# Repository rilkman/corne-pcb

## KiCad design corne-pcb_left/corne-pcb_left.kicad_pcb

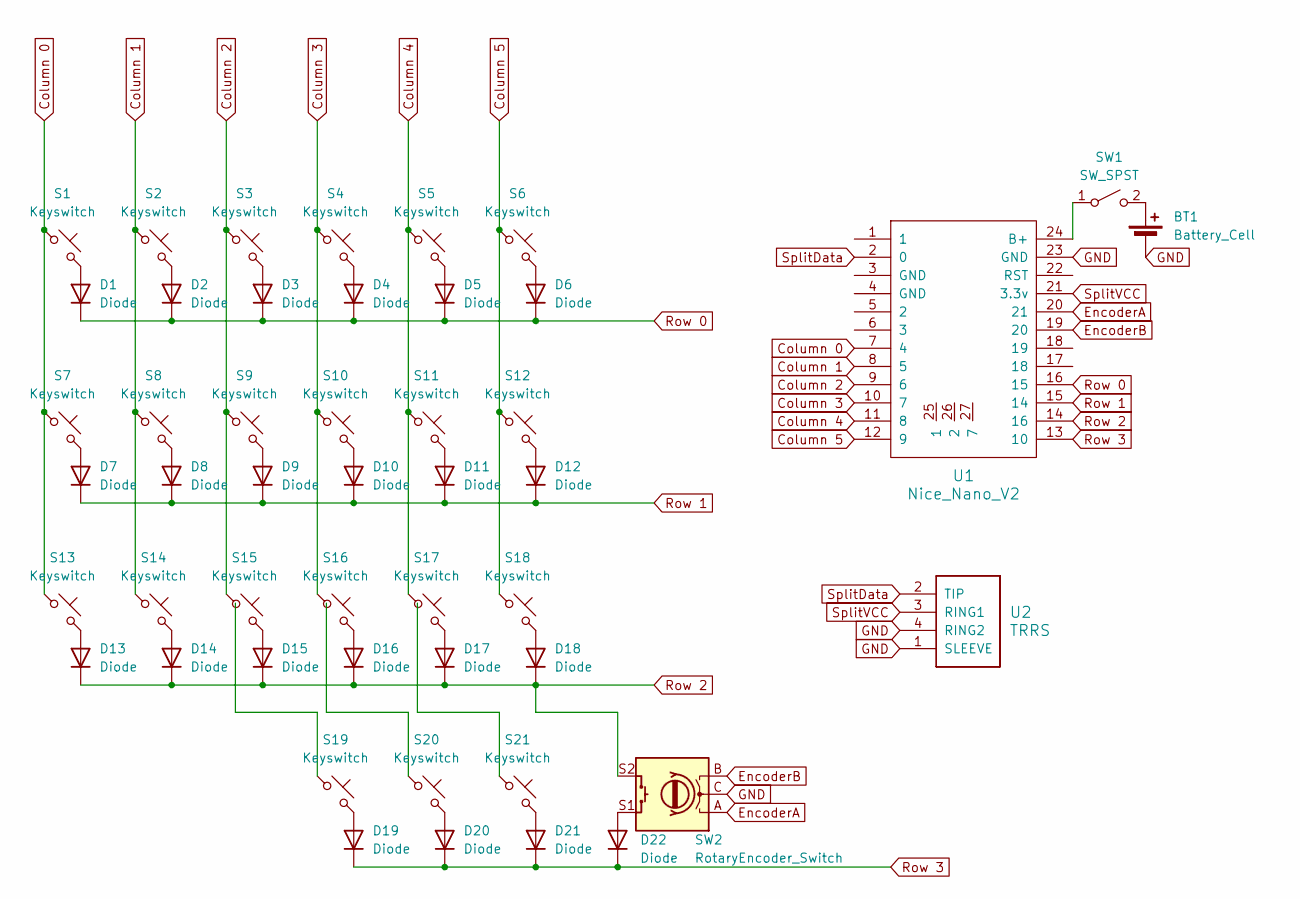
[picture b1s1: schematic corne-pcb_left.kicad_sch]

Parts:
BT1: Battery_Cell; JST_PH_S2B-PH-K_1x02_P2.00mm_Horizontal
D1, D2, D3, D4, D5, D6, D7, D8, D9, D10, D11, D12, D13, D14, D15, D16, D17, D18, D19, D20, D21, D22: Diode; Diode_SOD-123
S1, S2, S3, S4, S5, S6, S7, S8, S9, S10, S11, S12, S13, S14, S15, S16, S17, S18, S19, S20: Keyswitch; Hotswap_Choc_V1_1.00u
S21: Keyswitch; Hotswap_Choc_V1_1.50u_90deg
SW1: SW_SPST; SW_Slide_SPDT_Straight_CK_OS102011MS2Q
SW2: RotaryEncoder_Switch; Encoder_EC11_MX
U1: Nice_Nano_V2
U2: TRRS; TRRS_PJ-320A

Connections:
Column 0: S1.1, S7.1, S13.1, U1.7 (4)
Column 1: S2.1, S8.1, S14.1, U1.8 (5)
Column 2: S3.1, S9.1, S15.1, U1.9 (6)
Column 3: S4.1, S10.1, S16.1, U1.10 (7)
Column 4: S5.1, S11.1, S17.1, U1.11 (8)
Column 5: S6.1, S12.1, S18.1, U1.12 (9)
EncoderA: SW2.A, U1.20 (21)
EncoderB: SW2.B, U1.19 (20)
GND: BT1.2 (-), SW2.C, U1.23 (GND), U2.1 (SLEEVE), U2.4 (RING2)
unnamed: BT1.1 (+), SW1.2 (B)
unnamed: D1.2 (A), S1.2
unnamed: D2.2 (A), S2.2
unnamed: D3.2 (A), S3.2
unnamed: D4.2 (A), S4.2
unnamed: D5.2 (A), S5.2
unnamed: D6.2 (A), S6.2
unnamed: D7.2 (A), S7.2
unnamed: D8.2 (A), S8.2
unnamed: D9.2 (A), S9.2
unnamed: D10.2 (A), S10.2
unnamed: D11.2 (A), S11.2
unnamed: D12.2 (A), S12.2
unnamed: D13.2 (A), S13.2
unnamed: D14.2 (A), S14.2
unnamed: D15.2 (A), S15.2
unnamed: D16.2 (A), S16.2
unnamed: D17.2 (A), S17.2
unnamed: D18.2 (A), S18.2
unnamed: D19.2 (A), S19.2
unnamed: D20.2 (A), S20.2
unnamed: D21.2 (A), S21.2
unnamed: D22.2 (A), SW2.S1
unnamed: SW1.1 (A), U1.24 (B+)
Row 0: D1.1 (K), D2.1 (K), D3.1 (K), D4.1 (K), D5.1 (K), D6.1 (K), U1.16 (15)
Row 1: D7.1 (K), D8.1 (K), D9.1 (K), D10.1 (K), D11.1 (K), D12.1 (K), U1.15 (14)
Row 2: D13.1 (K), D14.1 (K), D15.1 (K), D16.1 (K), D17.1 (K), D18.1 (K), SW2.S2, U1.14 (16)
Row 3: D19.1 (K), D20.1 (K), D21.1 (K), D22.1 (K), U1.13 (10)
SplitData: U1.2 (0), U2.2 (TIP)
SplitVCC: U1.21 (3.3v), U2.3 (RING1)

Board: 2 copper layers, 48 parts (26 on the bottom side), 39 nets, no tracks yet.

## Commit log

2025-12-07 add encoder to left
